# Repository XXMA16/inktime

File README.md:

# InkTime

## Overview

InkTime is an open-source smartwatch project that aims to provide a customizable and feature-rich wearable device,
powered by the Nordic nRF52840 SoC. The device is designed to be energy-efficient, featuring a 1.54-inch e-ink display,
a 250mAh battery, an IMU for motion tracking, and a haptic driver for tactile feedback.

## Hardware Diagram

## Bill of Materials

| Quantity | Component         | Package      | Producer / Part            | Link         | Datasheet         |
|----------|-------------------|--------------|----------------------------|--------------|-------------------|
| 1        | SoC               | aQFN-73      | Nordic / nRF52840-QIAA     | [Link](TODO) | [Datasheet](TODO) |
| 1        | PMIC              | BGA-8        | TI / BQ25180YBGR           | [Link](TODO) | [Datasheet](TODO) |
| 1        | PMIC              | WLCSP-15     | Richtek / RT6160AWSC       | [Link](TODO) | [Datasheet](TODO) |
| 1        | Fuel Gauge IC     | TDFN-8       | Analog Devices / MAX17048  | [Link](TODO) | [Datasheet](TODO) |
| 1        | ESD Protection IC | SOT-23-6     | ST / USBLC6-2SC6Y          | [Link](TODO) | [Datasheet](TODO) |
| 1        | Haptic Driver     | BGA-9        | TI / DRV2605YZFR           | [Link](TODO) | [Datasheet](TODO) |
| 1        | IMU               | 12-pin LGA   | Bosch / BMA423             | [Link](TODO) | [Datasheet](TODO) |
| 1        | Antenna           | 3216 (1206)  | Johanson / 2.45GHz Antenna | [Link](TODO) | [Datasheet](TODO) |
| 1        | Connector         | FPC-24       | Molex / EPD Connector      | [Link](TODO) | [Datasheet](TODO) |
| 1        | Connector         | SMT          | Kinghelm / KH-TYPE-C-16P   | [Link](TODO) | [Datasheet](TODO) |
| 3        | Switch            | SMT (Button) | Panasonic / Tactile SW     | [Link](TODO) | [Datasheet](TODO) |
| 3        | Diode             | SOD-123      | ON Semi / MBR0530          | [Link](TODO) | [Datasheet](TODO) |
| 1        | N-MOSFET          | SC-70-3      | Vishay / SI1308EDL         | [Link](TODO) | [Datasheet](TODO) |
| 1        | P-MOSFET          | SOT-23       | Diodes Inc / DMG2305UX-7   | [Link](TODO) | [Datasheet](TODO) |

| Quantity | Component | Value     | Package | Producer | Link                                                                     | Datasheet                                                                                                                                                                                                                                                                                                                                                                                                                                                                                                                                                                                                                                                                                                                                                                                                                                                                                                                                                                                                                                                                                                                                                                                                                                                                              |
|----------|-----------|-----------|---------|----------|--------------------------------------------------------------------------|----------------------------------------------------------------------------------------------------------------------------------------------------------------------------------------------------------------------------------------------------------------------------------------------------------------------------------------------------------------------------------------------------------------------------------------------------------------------------------------------------------------------------------------------------------------------------------------------------------------------------------------------------------------------------------------------------------------------------------------------------------------------------------------------------------------------------------------------------------------------------------------------------------------------------------------------------------------------------------------------------------------------------------------------------------------------------------------------------------------------------------------------------------------------------------------------------------------------------------------------------------------------------------------|
| 1        | Jumper    | -         | SMD     | -        | [Link](TODO)                                                             | [Datasheet](TODO)                                                                                                                                                                                                                                                                                                                                                                                                                                                                                                                                                                                                                                                                                                                                                                                                                                                                                                                                                                                                                                                                                                                                                                                                                                                                      |
| 3        | Resistor  | 0         | 0201    | -        | [Link](TODO)                                                             | [Datasheet](TODO)                                                                                                                                                                                                                                                                                                                                                                                                                                                                                                                                                                                                                                                                                                                                                                                                                                                                                                                                                                                                                                                                                                                                                                                                                                                                      |
| 1        | Resistor  | 0.47R     | 0201    | -        | [Link](TODO)                                                             | [Datasheet](TODO)                                                                                                                                                                                                                                                                                                                                                                                                                                                                                                                                                                                                                                                                                                                                                                                                                                                                                                                                                                                                                                                                                                                                                                                                                                                                      |
| 1        | Resistor  | 2.2R      | 0201    | -        | [Link](TODO)                                                             | [Datasheet](TODO)                                                                                                                                                                                                                                                                                                                                                                                                                                                                                                                                                                                                                                                                                                                                                                                                                                                                                                                                                                                                                                                                                                                                                                                                                                                                      |
| 2        | Resistor  | 3.3K      | 0201    | -        | [Link](TODO)                                                             | [Datasheet](TODO)                                                                                                                                                                                                                                                                                                                                                                                                                                                                                                                                                                                                                                                                                                                                                                                                                                                                                                                                                                                                                                                                                                                                                                                                                                                                      |
| 2        | Resistor  | 5.1K      | 0201    | -        | [Link](TODO)                                                             | [Datasheet](TODO)                                                                                                                                                                                                                                                                                                                                                                                                                                                                                                                                                                                                                                                                                                                                                                                                                                                                                                                                                                                                                                                                                                                                                                                                                                                                      |
| 6        | Resistor  | 10K       | 0201    | -        | [Link](TODO)                                                             | [Datasheet](TODO)                                                                                                                                                                                                                                                                                                                                                                                                                                                                                                                                                                                                                                                                                                                                                                                                                                                                                                                                                                                                                                                                                                                                                                                                                                                                      |
| 3        | Capacitor | N.C.      | 0201    | -        | -                                                                        | ** -                                                                                                                                                                                                                                                                                                                                                                                                                                                                                                                                                                                                                                                                                                                                                                                                                                                                                                                                                                                                                                                                                                                                                                                                                                                                                   |
| 2        | Capacitor | 1pF       | 0201    | -        | [Link](TODO)                                                             | [Datasheet](TODO)                                                                                                                                                                                                                                                                                                                                                                                                                                                                                                                                                                                                                                                                                                                                                                                                                                                                                                                                                                                                                                                                                                                                                                                                                                                                      |
| 1        | Capacitor | 820pF     | 0201    | -        | [Link](TODO)                                                             | [Datasheet](TODO)                                                                                                                                                                                                                                                                                                                                                                                                                                                                                                                                                                                                                                                                                                                                                                                                                                                                                                                                                                                                                                                                                                                                                                                                                                                                      |
| 4        | Capacitor | 12pF      | 0201    | -        | [Link](TODO)                                                             | [Datasheet](TODO)                                                                                                                                                                                                                                                                                                                                                                                                                                                                                                                                                                                                                                                                                                                                                                                                                                                                                                                                                                                                                                                                                                                                                                                                                                                                      |
| 1        | Capacitor | 100pF     | 0201    | -        | [Link](TODO)                                                             | [Datasheet](TODO)                                                                                                                                                                                                                                                                                                                                                                                                                                                                                                                                                                                                                                                                                                                                                                                                                                                                                                                                                                                                                                                                                                                                                                                                                                                                      |
| 1        | Capacitor | 47nF      | 0201    | -        | [Link](TODO)                                                             | [Datasheet](TODO)                                                                                                                                                                                                                                                                                                                                                                                                                                                                                                                                                                                                                                                                                                                                                                                                                                                                                                                                                                                                                                                                                                                                                                                                                                                                      |
| 9        | Capacitor | 100nF     | 0201    | -        | [Link](TODO)                                                             | [Datasheet](TODO)                                                                                                                                                                                                                                                                                                                                                                                                                                                                                                                                                                                                                                                                                                                                                                                                                                                                                                                                                                                                                                                                                                                                                                                                                                                                      |
| 1        | Capacitor | 0.1uF/50V | 0201    | -        | [Link](TODO)                                                             | [Datasheet](TODO)                                                                                                                                                                                                                                                                                                                                                                                                                                                                                                                                                                                                                                                                                                                                                                                                                                                                                                                                                                                                                                                                                                                                                                                                                                                                      |
| 7        | Capacitor | 1uF       | 0402    | -        | [Link](TODO)                                                             | [Datasheet](TODO)                                                                                                                                                                                                                                                                                                                                                                                                                                                                                                                                                                                                                                                                                                                                                                                                                                                                                                                                                                                                                                                                                                                                                                                                                                                                      |
| 9        | Capacitor | 1uF/50V   | 0402    | -        | [Link](TODO)                                                             | [Datasheet](TODO)                                                                                                                                                                                                                                                                                                                                                                                                                                                                                                                                                                                                                                                                                                                                                                                                                                                                                                                                                                                                                                                                                                                                                                                                                                                                      |
| 5        | Capacitor | 4.7uF     | 0402    | -        | [Link](TODO)                                                             | [Datasheet](TODO)                                                                                                                                                                                                                                                                                                                                                                                                                                                                                                                                                                                                                                                                                                                                                                                                                                                                                                                                                                                                                                                                                                                                                                                                                                                                      |
| 1        | Capacitor | 4.7uF/25V | 0402    | -        | [Link](TODO)                                                             | [Datasheet](TODO)                                                                                                                                                                                                                                                                                                                                                                                                                                                                                                                                                                                                                                                                                                                                                                                                                                                                                                                                                                                                                                                                                                                                                                                                                                                                      |
| 3        | Capacitor | 10uF      | 0402    | -        | [Link](TODO)                                                             | [Datasheet](TODO)                                                                                                                                                                                                                                                                                                                                                                                                                                                                                                                                                                                                                                                                                                                                                                                                                                                                                                                                                                                                                                                                                                                                                                                                                                                                      |
| 2        | Capacitor | 22uF      | 0402    | -        | [Link](TODO)                                                             | [Datasheet](TODO)                                                                                                                                                                                                                                                                                                                                                                                                                                                                                                                                                                                                                                                                                                                                                                                                                                                                                                                                                                                                                                                                                                                                                                                                                                                                      |
| 1        | Inductor  | 3.9nH     | 0402    | -        | [Link](TODO)                                                             | [Datasheet](TODO)                                                                                                                                                                                                                                                                                                                                                                                                                                                                                                                                                                                                                                                                                                                                                                                                                                                                                                                                                                                                                                                                                                                                                                                                                                                                      |
| 1        | Inductor  | 470nH     | 1008    | Cjiang   | [Link](https://jlcpcb.com/partdetail/6763488-FTC252012SR47MBCA/C5832368) | [Datasheet](https://jlc-prod-smt.oss-eu-central-1.aliyuncs.com/smtDataManualFile/8602848214240948224-C5832368.pdf?response-content-disposition=attachment%3B%20filename%3DC5832368.pdf%3B%20filename%2A%3DUTF-8%27%27C5832368.pdf&x-oss-date=20260420T155325Z&x-oss-expires=1800&x-oss-security-token=CAISgAN1q6Ft5B2yfSjIr5rSCtj%2Fo6dC%2BbGGNkGChjMYerl0mf2akzz2IHhMdHJsAOodtv0%2FmmhT6PkclqRLcbhpcmfjV%2BZHzLB8qYFskT1z4J7b16cNrbH4M4H6aXeirtuwDsz9SNTCALjPD3nPii50x5bjaDymRCbLGJaViJlhHLN1Ow6jdmhpCctxLAlvo9NgFxm3D%2Fu2NQPwiWf9FVdhvhEG6Vly8qOi2MaRmFy8yFTx0b0SvJ%2BjYMrmPctoN9JnSdC5mfdzau3a1TJ84gRD0a5wkaVA1zbDs5bfISEIuUzebreLqY03dV4mOvdqIcMe8qigz88fk%2FfIioH6xyxKOexoSCnFTOiiupCcQLPyao9jLu6iayqViY7QaIOTqQohZmkAMwVOasAsI3Ngh4zF97Qt0cVNkXO9gWfLI8DtuMleWoroXextznSgc5lCkRRYwGs1287ugXlSQzo890KPDAEovaKCnZ2ZSfh7Y4sNknI6i%2Bfc2Se2MIkIM0KR4aKWD5sagAFKmiegLXY5feEbLYeCAmVE74YudDbqKoQ88ESR1e%2B42dXounyOYCRSYvo%2FT572eiHhDatupWrWOYBuvJfZpePknbuE8s%2B9jEg9KM0kWXFXEacIIbF5TeTZBNtRDJxsy02ORP5MUB9y8Q1uyuTYfNhwCQ%2B5T3JbDOX0%2BPOrZrTLbSAA&x-oss-signature-version=OSS4-HMAC-SHA256&x-oss-credential=STS.NYgAbKNxcNsm4g3b3Mv6Xv81q%2F20260420%2Feu-central-1%2Foss%2Faliyun_v4_request&x-oss-signature=a349516f90567f817aa69e514ac3e996d2db1f907bb8816a9e576956e31e9d0f) |
| 1        | Inductor  | 10uH      | 0402    | -        | [Link](TODO)                                                             | [Datasheet](TODO)                                                                                                                                                                                                                                                                                                                                                                                                                                                                                                                                                                                                                                                                                                                                                                                                                                                                                                                                                                                                                                                                                                                                                                                                                                                                      |
| 1        | Inductor  | 15uH      | 0402    | -        | [Link](TODO)                                                             | [Datasheet](TODO)                                                                                                                                                                                                                                                                                                                                                                                                                                                                                                                                                                                                                                                                                                                                                                                                                                                                                                                                                                                                                                                                                                                                                                                                                                                                      |
| 1        | Inductor  | 68uH      | 4848    | Wurth    | [Link](TODO)                                                             | [Datasheet](https://www.we-online.com/components/products/datasheet/744043003.pdf)                                                                                                                                                                                                                                                                                                                                                                                                                                                                                                                                                                                                                                                                                                                                                                                                                                                                                                                                                                                                                                                                                                                                                                                                     |
| 1        | Crystal   | 32.768kHz | SMD     | Nordic   | [Link](TODO)                                                             | [Datasheet](TODO)                                                                                                                                                                                                                                                                                                                                                                                                                                                                                                                                                                                                                                                                                                                                                                                                                                                                                                                                                                                                                                                                                                                                                                                                                                                                      |
| 1        | Crystal   | 32MHz     | SMD     | Nordic   | [Link](TODO)                                                             | [Datasheet](TODO)                                                                                                                                                                                                                                                                                                                                                                                                                                                                                                                                                                                                                                                                                                                                                                                                                                                                                                                                                                                                                                                                                                                                                                                                                                                                      |

## SoC pin configuration

- **P$AD22 (SWO)** - connection to TP_SWO for debugging
- **P$AA24 (SWDCLK)** - connection for SWD, for the purpose of clock debugging
- **P$AC24 (SWDIO)** - SWD input/output connection
- **P$AC13 (RESET)** - connection to TP_RESET and SWD for resetting the component
- **P$Y23 (P1.01)** - E-Paper Drive Circuit
- **P$AD12 (EPD_BUSY)** - indicates whether the screen is busy displaying or not
- **P$AD10 (EPD_DC)** - E-Paper Display Data/Command selection for SPI connection
- **P$K2 (EPD_CS)** - E-Paper Display Chip Select (SPI)
- **P$AD12 (EPD_RST)** - E-Paper Display Reset for SPI connection
- **P$P13 (MOSI)** - data for screen SPI connection
- **P$A12 (SCK)** - clock for screen SPI connection
- **P$L1 (SDA)** - I2C data for PMIC, Fuel Gauge, IMU
- **P$M2 (SCL)** - I2C clock for PMIC, Fuel Gauge, IMU
- **P$AD8 (P0.13)** - GPIO for the up button.
- **P$AC9 (P0.14)** - GPIO for the middle button.
- **P$W24 (P1.02)** - GPIO for the down button.
- **P$AD6 (D+)** - positive differential trace to the ESD Protection
- **P$AD4 (D-)** - negative differential trace to the ESD Protection
- **P$AD2 (VBUS)** - connection to the VBUS signal of the USB-C Connector
- **P$U1 (HAPTIC_EN)** - Haptic Driver enable/disable
- **P$T2 (PMIC_INT)** - PMIC LiPo battery interrupt
- **P$N1 (IMU_INT1)** - IMU interrupt
- **P$P2 (IMU_INT2)** - IMU interrupt
- **P\$F2 & P$D2** - 32 kHz clock
- **P\$A23 & P$A24** - 32 MHz clock
- **P$J24 (ALERT)** - Fuel Gauge circuit alert
- **P\$H23 & P$F23** - wireless transmission via the antenna

## PCB Layout

### Stackup

1. Signal and Power
2. Ground Plane
3. Power
4. Signal

Thickness: 1mm

- solder mask: 0.0254mm
- surface finish: Hasl 0.02mm
- copper weight: 1oz
- layers: 0.035mm
- outer dielectrics: 0.128mm
- inner dielectric: 0.5132mm

Via Stitching

- drill: 0.35mm diameter
- spacing: 1.8mm
- offset: 0.6mm from the edge of the board

### Component Placement

The **antenna** is placed close to the right edge of the board, with a cutout in the copper pours on the entire right
side of the board. There is also a cutout in the PCB itself under the unconnected pad of the antenna.  
The **PI** network is placed as close as possible to the antenna, an additional capacitor may be placed to better tune
the antenna.  
Light propagates at around half its speed in a vacuum in FR4. A simple calculation gives a value of around:

$$\frac{\lambda}{4} = \frac{c_{FR4}}{4f} \approx \frac{1.4 \times 10^8 m/s}{4 \times 2.4 \times 10^9 Hz} \approx 14.6 mm$$

The trace connecting the PI network to the nRF52840 pin is 5mm long, thus the antenna should work properly.  
It would be better to use a grounded coplanar waveguide for the trace, maybe calculate the width using JLCPCB's online
calculator and use one of their layer stackups instead of the one described above, but this should suffice
for a first iteration of the board.

The decoupling capacitors are placed as possible to the power pins of the IC components and in between the power line
and the pin itself.  
The crystals are also placed close to the pins of the SoC, with the load capacitors traces matched in length and as
short as possible.  
The inductor for the E-Paper Drive Circuit is placed far from any signal lines to avoid interference, even though
it is in a shielded package.

### Approved Errors

Most of the errors are related to drill sizes or blind to micro via ratios. These are all approved since, although it
will be more expensive to manufacture, JLCPCB is still able to drill the holes and make the vias.  
Thus these kind of errors can be safely ignored.

Since the nRF52840 is a BGA package, some of the pins *must* have vias in the pad. Some of these cause Fusion to give
a copper clearance error, but, again, JLCPCB is able to manufacture the board so they can also be approved.

## Mechanical Design

The buzzer is placed on the back of the board, in the lower left corner (when worn on the left wrist).

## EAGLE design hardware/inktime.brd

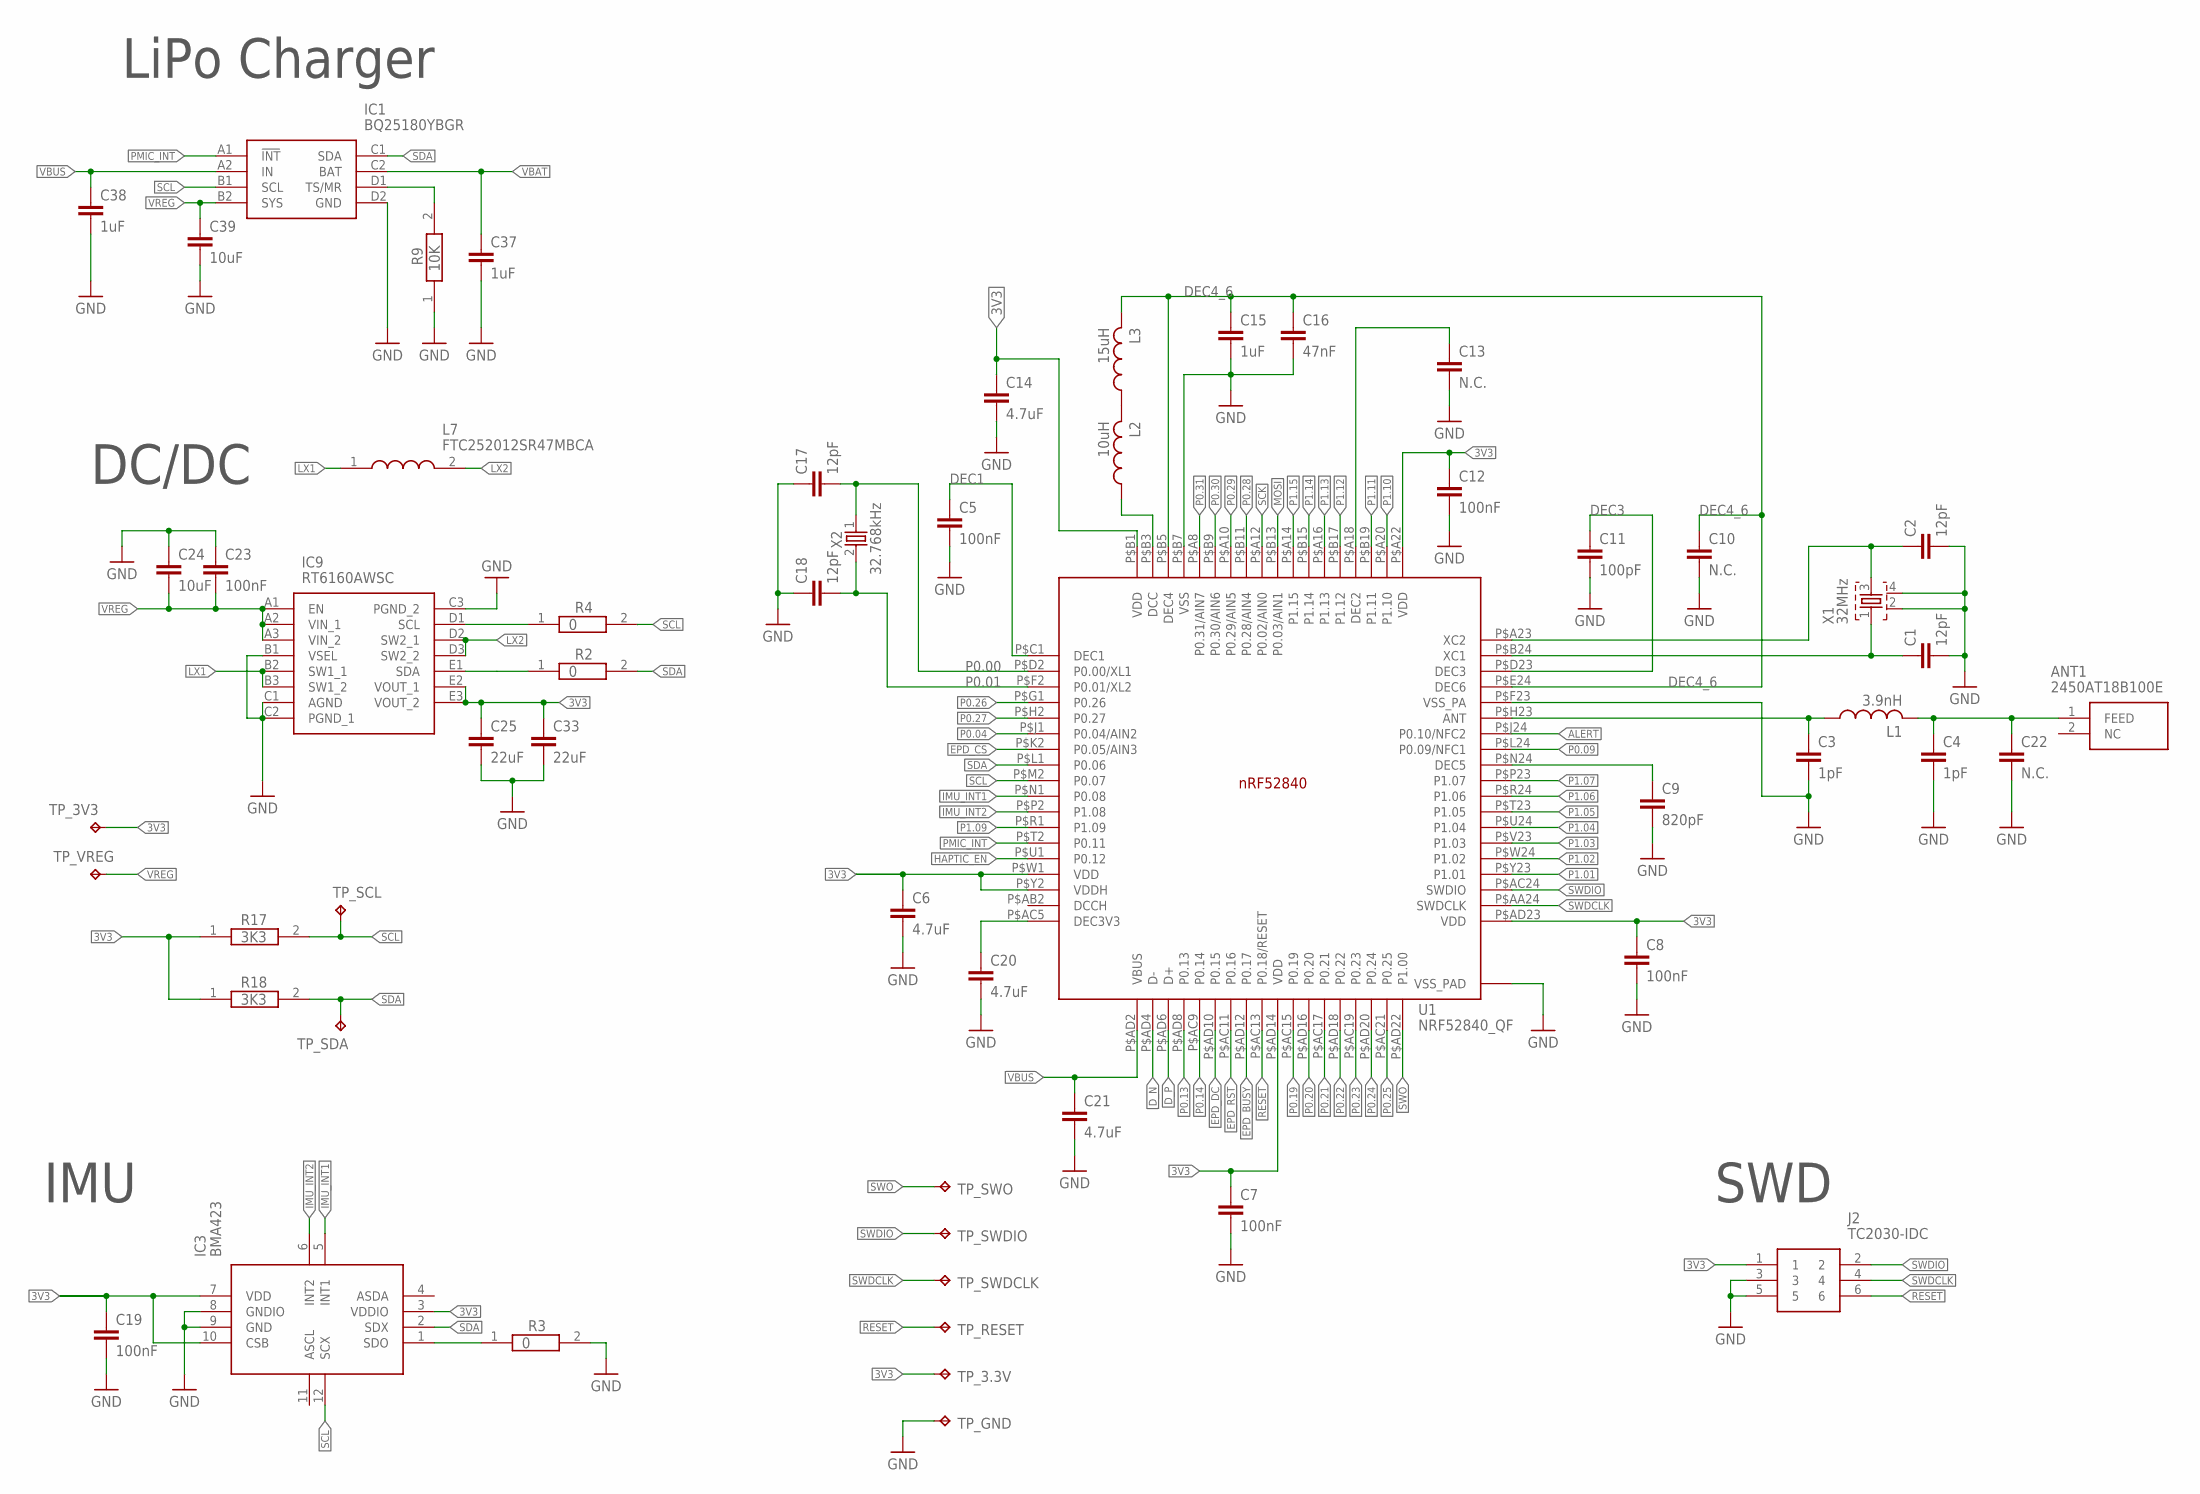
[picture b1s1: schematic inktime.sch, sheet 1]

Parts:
ANT1: 2450AT18B100E; 2450AT18B100E_ANTC3216X140N
C1, C2, C17, C18: 12pF; NORDIC_NRF_3_RESC0201_L
C3, C4: 1pF; NORDIC_NRF_3_RESC0201_L
C5, C7, C8, C12, C19, C23: 100nF; NORDIC_NRF_3_RESC0201_L
C6, C14, C20, C21: 4.7uF; NORDIC_NRF_3_RESC0402_L
C9: 820pF; NORDIC_NRF_3_RESC0201_L
C10, C13, C22: N.C.; NORDIC_NRF_3_RESC0201_L
C11: 100pF; NORDIC_NRF_3_RESC0201_L
C15, C37, C38: 1uF; NORDIC_NRF_3_RESC0402_L
C16: 47nF; NORDIC_NRF_3_RESC0201_L
C24, C39: 10uF; NORDIC_NRF_3_RESC0402_L
C25, C33: 22uF; NORDIC_NRF_3_RESC0402_L
IC1: BQ25180YBGR; BQ25180YBGR_BGA8C40P2X4_100X155X50
IC3: BMA423; BMA423_BMA423
IC9: RT6160AWSC; RT6160AWSC_BGA15C40P3X5_140X230X60
J2: TC2030-IDC; TC2030-IDC_TC2030IDC
L1: 3.9nH; NORDIC_NRF_2_RESC0402_L
L2: 10uH; NORDIC_NRF_2_RESC0402_L
L3: 15uH; NORDIC_NRF_2_RESC0402_L
L7: FTC252012SR47MBCA; MLP2016SR47MT0S1_INDC2016X100N
R2, R3, R4: 0; CPF0201D7K68C1_0201
R9: 10K; CPF0201D7K68C1_0201
R17, R18: 3K3; CPF0201D7K68C1_0201
TP_3.3V, TP_3V3: HECTOR_WATCH_1_TPTP20R; HECTOR_WATCH_1_TP20R
TP_GND: HECTOR_WATCH_1_TPTP20R; HECTOR_WATCH_1_TP20R
TP_RESET: HECTOR_WATCH_1_TPTP20R; HECTOR_WATCH_1_TP20R
TP_SCL: HECTOR_WATCH_1_TPTP20R; HECTOR_WATCH_1_TP20R
TP_SDA: HECTOR_WATCH_1_TPTP20R; HECTOR_WATCH_1_TP20R
TP_SWDCLK: HECTOR_WATCH_1_TPTP20R; HECTOR_WATCH_1_TP20R
TP_SWDIO: HECTOR_WATCH_1_TPTP20R; HECTOR_WATCH_1_TP20R
TP_SWO: HECTOR_WATCH_1_TPTP20R; HECTOR_WATCH_1_TP20R
TP_VREG: HECTOR_WATCH_1_TPTP20R; HECTOR_WATCH_1_TP20R
U1: NRF52840_QF; NORDIC_NRF_4_AQFN50P700X700X85_HS-74N
X1: 32MHz; NORDIC_NRF_BT-XTAL_2016_N
X2: 32.768kHz; NORDIC_NRF_1_XTAL_3215_N

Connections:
3V3: C6.1, C7.1, C8.1, C12.1, C14.1, C19.1, C25.1, C33.1, IC3.3 (VDDIO), IC3.7 (VDD), IC3.10 (CSB), IC9.E2 (VOUT_1), IC9.E3 (VOUT_2), J2.1, R17.1, R18.1, TP_3.3V.TP, TP_3V3.TP, U1.P$A22 (VDD), U1.P$AD14 (VDD), U1.P$AD23 (VDD), U1.P$B1 (VDD), U1.P$W1 (VDD), U1.P$Y2 (VDDH); also elsewhere on the board
ALERT: U1.P$J24 (P0.10/NFC2); also elsewhere on the board
DEC1: C5.1, U1.P$C1 (DEC1)
DEC3: C11.1, U1.P$D23 (DEC3)
DEC4_6: C10.1, C15.1, C16.1, L3.2, U1.P$B5 (DEC4), U1.P$E24 (DEC6)
D_N: U1.P$AD4 (D-); also elsewhere on the board
D_P: U1.P$AD6 (D+); also elsewhere on the board
EPD_BUSY: U1.P$AD12 (P0.17); also elsewhere on the board
EPD_CS: U1.P$K2 (P0.05/AIN3); also elsewhere on the board
EPD_DC: U1.P$AD10 (P0.15); also elsewhere on the board
EPD_RST: U1.P$AC11 (P0.16); also elsewhere on the board
GND: C1.2, C2.2, C3.2, C4.2, C5.2, C6.2, C7.2, C8.2, C9.2, C10.2, C11.2, C12.2, C13.2, C14.2, C15.2, C16.2, C17.1, C18.1, C19.2, C20.2, C21.2, C22.2, C23.1, C24.1, C25.2, C33.2, C37.2, C38.2, C39.2, IC1.D2 (GND), IC3.8 (GNDIO), IC3.9 (GND), IC9.B1 (VSEL), IC9.C1 (AGND), IC9.C2 (PGND_1), IC9.C3 (PGND_2), J2.3, J2.5, R3.2, R9.1, TP_GND.TP, U1.P$74 (VSS_PAD), U1.P$75 (VSS_PAD), U1.P$76 (VSS_PAD), U1.P$77 (VSS_PAD), U1.P$78 (VSS_PAD), U1.P$79 (VSS_PAD), U1.P$80 (VSS_PAD), U1.P$81 (VSS_PAD), U1.P$82 (VSS_PAD), U1.P$83 (VSS_PAD), U1.P$84 (VSS_PAD), U1.P$85 (VSS_PAD), U1.P$86 (VSS_PAD), U1.P$87 (VSS_PAD), U1.P$88 (VSS_PAD), U1.P$89 (VSS_PAD), U1.P$90 (VSS_PAD), U1.P$B7 (VSS), U1.P$F23 (VSS_PA), X1.2, X1.4; also elsewhere on the board
HAPTIC_EN: U1.P$U1 (P0.12); also elsewhere on the board
IMU_INT1: IC3.5 (INT1), U1.P$N1 (P0.08)
IMU_INT2: IC3.6 (INT2), U1.P$P2 (P1.08)
LX1: IC9.B2 (SW1_1), IC9.B3 (SW1_2), L7.1
LX2: IC9.D2 (SW2_1), IC9.D3 (SW2_2), L7.2
MOSI: U1.P$B13 (P0.03/AIN1); also elsewhere on the board
unnamed: IC1.D1 (TS/MR), R9.2
unnamed: ANT1.1 (FEED), C4.1, C22.1, L1.2
unnamed: C2.1, U1.P$A23 (XC2), X1.3
unnamed: C1.1, U1.P$B24 (XC1), X1.1
unnamed: IC9.E1 (SDA), R2.1
unnamed: IC9.D1 (SCL), R4.1
unnamed: C13.1, U1.P$A18 (DEC2)
unnamed: IC3.1 (SDO), R3.1
unnamed: C20.1, U1.P$AC5 (DEC3V3)
unnamed: L2.1, U1.P$B3 (DCC)
unnamed: L2.2, L3.1
unnamed: C9.1, U1.P$N24 (DEC5)
unnamed: C3.1, L1.1, U1.P$H23 (ANT)
P0.00: C17.2, U1.P$D2 (P0.00/XL1), X2.1
P0.01: C18.2, U1.P$F2 (P0.01/XL2), X2.2
P0.04: U1.P$J1 (P0.04/AIN2)
P0.09: U1.P$L24 (P0.09/NFC1)
P0.13: U1.P$AD8 (P0.13); also elsewhere on the board
P0.14: U1.P$AC9 (P0.14); also elsewhere on the board
P0.19: U1.P$AC15 (P0.19)
P0.20: U1.P$AD16 (P0.20)
P0.21: U1.P$AC17 (P0.21)
P0.22: U1.P$AD18 (P0.22)
P0.23: U1.P$AC19 (P0.23)
P0.24: U1.P$AD20 (P0.24)
P0.25: U1.P$AC21 (P0.25)
P0.26: U1.P$G1 (P0.26)
P0.27: U1.P$H2 (P0.27)
P0.28: U1.P$B11 (P0.28/AIN4)
P0.29: U1.P$A10 (P0.29/AIN5)
P0.30: U1.P$B9 (P0.30/AIN6)
P0.31: U1.P$A8 (P0.31/AIN7)
P1.01: U1.P$Y23 (P1.01); also elsewhere on the board
P1.02: U1.P$W24 (P1.02); also elsewhere on the board
P1.03: U1.P$V23 (P1.03)
P1.04: U1.P$U24 (P1.04)
P1.05: U1.P$T23 (P1.05)
P1.06: U1.P$R24 (P1.06)
P1.07: U1.P$P23 (P1.07)
P1.09: U1.P$R1 (P1.09)
P1.10: U1.P$A20 (P1.10)
P1.11: U1.P$B19 (P1.11)
P1.12: U1.P$B17 (P1.12)
P1.13: U1.P$A16 (P1.13)
P1.14: U1.P$B15 (P1.14)
P1.15: U1.P$A14 (P1.15)
PMIC_INT: IC1.A1 (!INT), U1.P$T2 (P0.11)
RESET: J2.6, TP_RESET.TP, U1.P$AC13 (P0.18/RESET)
SCK: U1.P$A12 (P0.02/AIN0); also elsewhere on the board
SCL: IC1.B1 (SCL), IC3.12 (SCX), R4.2, R17.2, TP_SCL.TP, U1.P$M2 (P0.07); also elsewhere on the board
SDA: IC1.C1 (SDA), IC3.2 (SDX), R2.2, R18.2, TP_SDA.TP, U1.P$L1 (P0.06); also elsewhere on the board
SWDCLK: J2.4, TP_SWDCLK.TP, U1.P$AA24 (SWDCLK)
SWDIO: J2.2, TP_SWDIO.TP, U1.P$AC24 (SWDIO)
SWO: TP_SWO.TP, U1.P$AD22 (P1.00)
VBAT: C37.1, IC1.C2 (BAT); also elsewhere on the board
VBUS: C21.1, C38.1, IC1.A2 (IN), U1.P$AD2 (VBUS); also elsewhere on the board
VREG: C23.2, C24.2, C39.1, IC1.B2 (SYS), IC9.A1 (EN), IC9.A2 (VIN_1), IC9.A3 (VIN_2), TP_VREG.TP

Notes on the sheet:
LiPo Charger
DC/DC
IMU
SWD

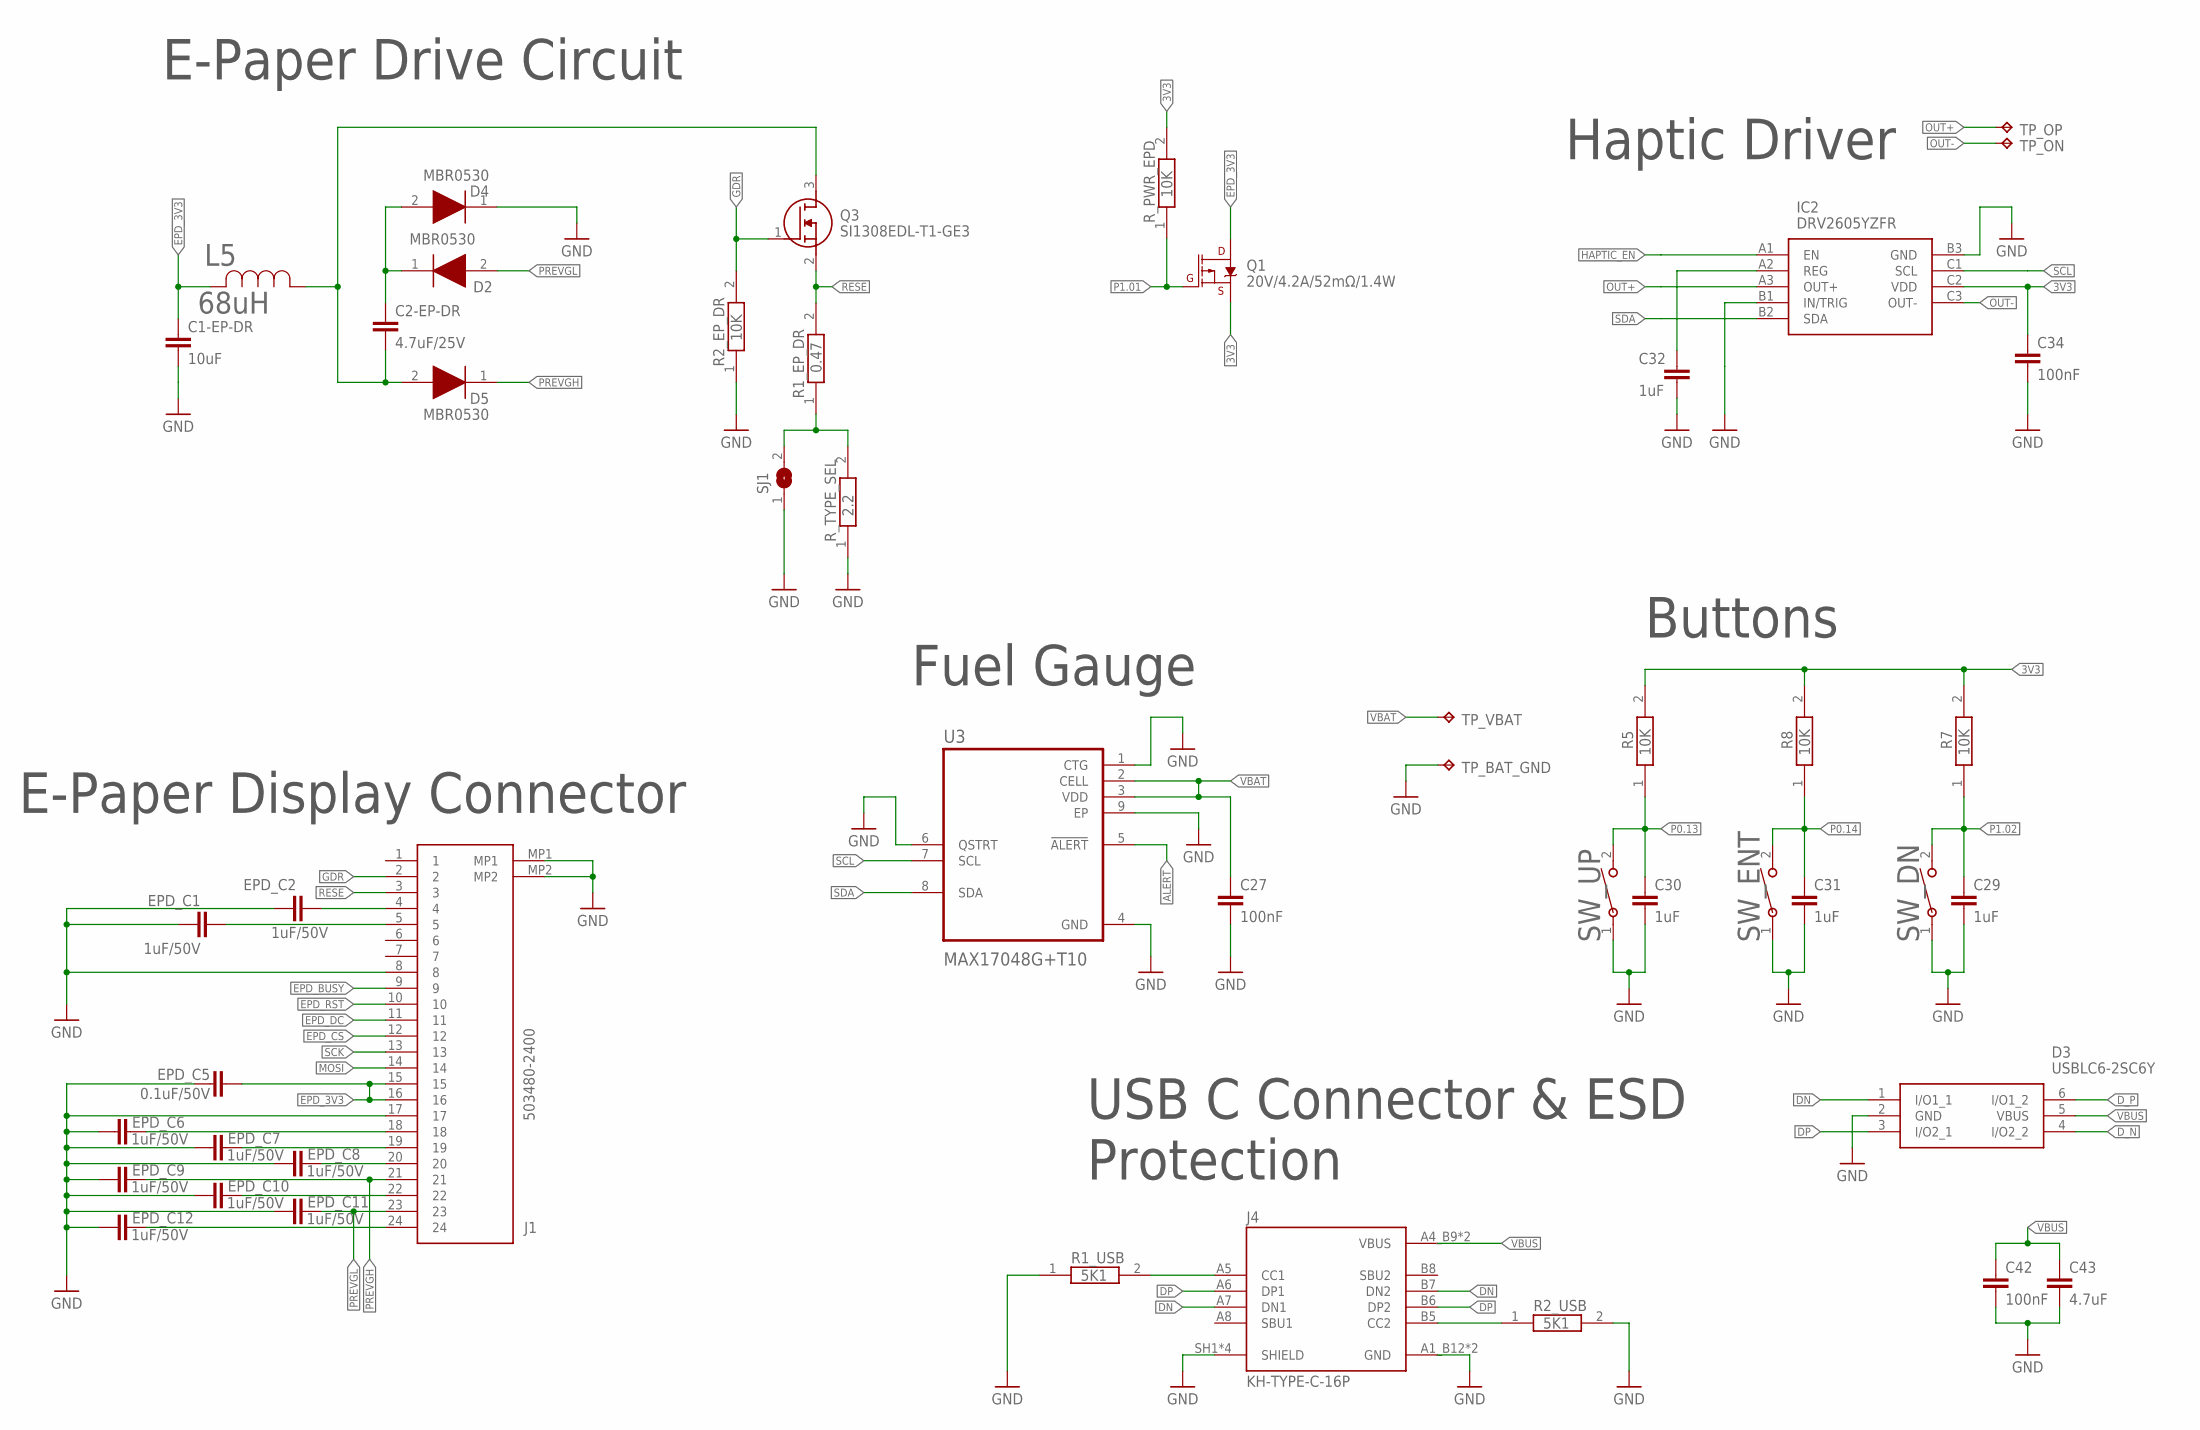
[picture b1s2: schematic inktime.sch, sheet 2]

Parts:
C1-EP-DR: 10uF; NORDIC_NRF_3_RESC0402_L
C2-EP-DR: 4.7uF/25V; NORDIC_NRF_3_RESC0402_L
C27, C34, C42: 100nF; NORDIC_NRF_3_RESC0201_L
C29, C30, C31, C32: 1uF; NORDIC_NRF_3_RESC0402_L
C43: 4.7uF; NORDIC_NRF_3_RESC0402_L
D2, D4, D5: MBR0530; ESP32_C6_LIBRARY_5_SOD3716X135N
D3: USBLC6-2SC6Y; ESP32_C6_LIBRARY_3_SOT95P280X145-6N
EPD_C1, EPD_C2, EPD_C6, EPD_C7, EPD_C8, EPD_C9, EPD_C10, EPD_C11, EPD_C12: 1uF/50V; NORDIC_NRF_3_RESC0402_L
EPD_C5: 0.1uF/50V; NORDIC_NRF_3_RESC0201_L
IC2: DRV2605YZFR; DRV2605YZFR_BGA9C50P3X3_144X144X62
J1: 503480-2400; 503480-2400_5034802400
J4: KH-TYPE-C-16P; KH-TYPE-C-16P_KINGHELM_KH-TYPE-C-16P
L5: 68uH; ESP32_C6_LIBRARY_2_IND_4828-WE-TPC_WRE
Q1: 20V/4.2A/52mΩ/1.4W; ESP32_C6_LIBRARY_4_ESP32_C6_LIBRARY_4_ESP32_C6_LIBRARY_4_ES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
Q3: SI1308EDL-T1-GE3; ESP32_C6_LIBRARY_6_SOT65P210X110-3N
R1_EP_DR: 0.47; CPF0201D7K68C1_0201
R1_USB, R2_USB: 5K1; CPF0201D7K68C1_0201
R2_EP_DR, R5, R7, R8: 10K; CPF0201D7K68C1_0201
R_PWR_EPD: 10K; CPF0201D7K68C1_0201
R_TYPE_SEL: 2.2; CPF0201D7K68C1_0201
SJ1: ESP32_C6_LIBRARY_7_JUMPER_SJ
SW_DN: 2025-10-22_07-23-44_LIBRARY_EVP-AKE31ASW_EVP-AKE3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; 2025-10-22_07-23-44_LIBRARY_SW_EVP-AKE31A_PAN
SW_ENT: 2025-10-22_07-23-44_LIBRARY_EVP-AKE31ASW_EVP-AKE3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; 2025-10-22_07-23-44_LIBRARY_SW_EVP-AKE31A_PAN
SW_UP: 2025-10-22_07-23-44_LIBRARY_EVP-AKE31ASW_EVP-AKE3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; 2025-10-22_07-23-44_LIBRARY_SW_EVP-AKE31A_PAN
TP_BAT_GND: HECTOR_WATCH_1_TPTP20R; HECTOR_WATCH_1_TP20R
TP_ON: HECTOR_WATCH_1_TPTP20R; HECTOR_WATCH_1_TP20R
TP_OP: HECTOR_WATCH_1_TPTP20R; HECTOR_WATCH_1_TP20R
TP_VBAT: HECTOR_WATCH_1_TPTP20R; HECTOR_WATCH_1_TP20R
U3: MAX17048G+T10; ESP32_C6_LIBRARY_SON50P200X200X80-9N

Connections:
3V3: C34.1, IC2.C2 (VDD), Q1.2 (S), R5.2, R7.2, R8.2, R_PWR_EPD.2; also elsewhere on the board
ALERT: U3.5 (!ALERT); also elsewhere on the board
DN: D3.1 (I/O1_1), J4.A7 (DN1), J4.B7 (DN2)
DP: D3.3 (I/O2_1), J4.A6 (DP1), J4.B6 (DP2)
D_N: D3.4 (I/O2_2); also elsewhere on the board
D_P: D3.6 (I/O1_2); also elsewhere on the board
EPD_3V3: C1-EP-DR.1, EPD_C5.2, J1.15, J1.16, L5.2, Q1.3 (D)
EPD_BUSY: J1.9; also elsewhere on the board
EPD_CS: J1.12; also elsewhere on the board
EPD_DC: J1.11; also elsewhere on the board
EPD_RST: J1.10; also elsewhere on the board
GDR: J1.2, Q3.1 (G), R2_EP_DR.2
GND: C1-EP-DR.2, C27.2, C29.2, C30.2, C31.2, C32.2, C34.2, C42.2, C43.2, D3.2 (GND), D4.1 (K), EPD_C1.1, EPD_C2.1, EPD_C5.1, EPD_C6.1, EPD_C7.1, EPD_C8.1, EPD_C9.1, EPD_C10.1, EPD_C11.1, EPD_C12.1, IC2.B1 (IN/TRIG), IC2.B3 (GND), J1.8, J1.17, J1.MP1, J1.MP2, J4.A1_B12 (GND), J4.A12_B1 (GND), J4.SH1 (SHIELD), J4.SH2 (SHIELD), J4.SH3 (SHIELD), J4.SH4 (SHIELD), R1_USB.1, R2_EP_DR.1, R2_USB.2, R_TYPE_SEL.1, SJ1.1, SW_DN.1, SW_ENT.1, SW_UP.1, TP_BAT_GND.TP, U3.1 (CTG), U3.4 (GND), U3.6 (QSTRT), U3.9 (EP); also elsewhere on the board
HAPTIC_EN: IC2.A1 (EN); also elsewhere on the board
MOSI: J1.14; also elsewhere on the board
unnamed: EPD_C2.2, J1.4
unnamed: C2-EP-DR.1, D2.1 (K), D4.2 (A)
unnamed: C2-EP-DR.2, D5.2 (A), L5.1, Q3.3 (D)
unnamed: EPD_C1.2, J1.5
unnamed: R1_EP_DR.1, R_TYPE_SEL.2, SJ1.2
unnamed: EPD_C6.2, J1.18
unnamed: EPD_C7.2, J1.19
unnamed: EPD_C8.2, J1.20
unnamed: EPD_C10.2, J1.22
unnamed: C32.1, IC2.A2 (REG)
unnamed: EPD_C12.2, J1.24
unnamed: J4.B5 (CC2), R2_USB.1
unnamed: J4.A5 (CC1), R1_USB.2
OUT+: IC2.A3 (OUT+), TP_OP.TP
OUT-: IC2.C3 (OUT-), TP_ON.TP
P0.13: C30.1, R5.1, SW_UP.2; also elsewhere on the board
P0.14: C31.1, R8.1, SW_ENT.2; also elsewhere on the board
P1.01: Q1.1 (G), R_PWR_EPD.1; also elsewhere on the board
P1.02: C29.1, R7.1, SW_DN.2; also elsewhere on the board
PREVGH: D5.1 (K), EPD_C9.2, J1.21
PREVGL: D2.2 (A), EPD_C11.2, J1.23
RESE: J1.3, Q3.2 (S), R1_EP_DR.2
SCK: J1.13; also elsewhere on the board
SCL: IC2.C1 (SCL), U3.7 (SCL); also elsewhere on the board
SDA: IC2.B2 (SDA), U3.8 (SDA); also elsewhere on the board
VBAT: C27.1, TP_VBAT.TP, U3.2 (CELL), U3.3 (VDD); also elsewhere on the board
VBUS: C42.1, C43.1, D3.5 (VBUS), J4.A4_B9 (VBUS), J4.A9_B4 (VBUS); also elsewhere on the board

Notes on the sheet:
E-Paper Drive Circuit
E-Paper Display Connector
Fuel Gauge
USB C Connector & ESD Protection
Buttons
Haptic Driver

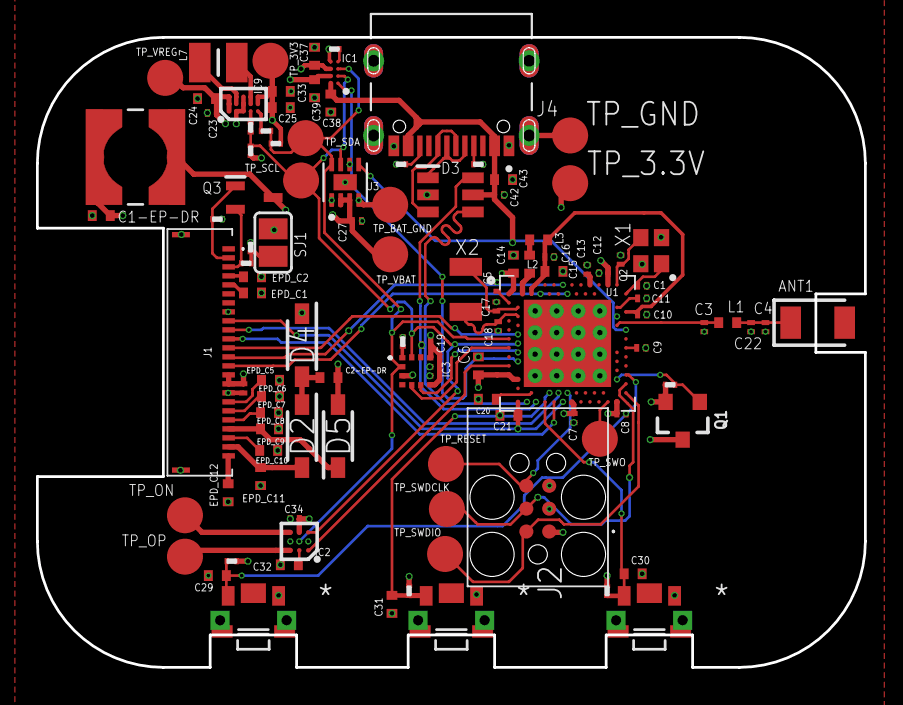
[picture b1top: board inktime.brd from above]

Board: 4 copper layers, 46.0 x 35.0 mm, 105 parts (0 on the bottom side), 70 nets.

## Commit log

2026-04-10 ceva sa fie
2026-04-14 PCB almost done
2026-04-15 Routing almost done
2026-04-17 Routing done
2026-04-20 Minor changes to schematic and PCB
2026-04-20 README, manufacturing, 3D's
2026-04-22 Added schematic pdf

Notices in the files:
parts and their libraries:
COPYRIGHT: Copyright (C) 2024 Ultra Librarian. All rights reserved.
COPYRIGHT: Copyright (C) 2025 Ultra Librarian. All rights reserved.
